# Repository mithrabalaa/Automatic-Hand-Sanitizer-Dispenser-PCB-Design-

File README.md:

# Automatic-Hand-Sanitizer-Dispenser-PCB-Design-

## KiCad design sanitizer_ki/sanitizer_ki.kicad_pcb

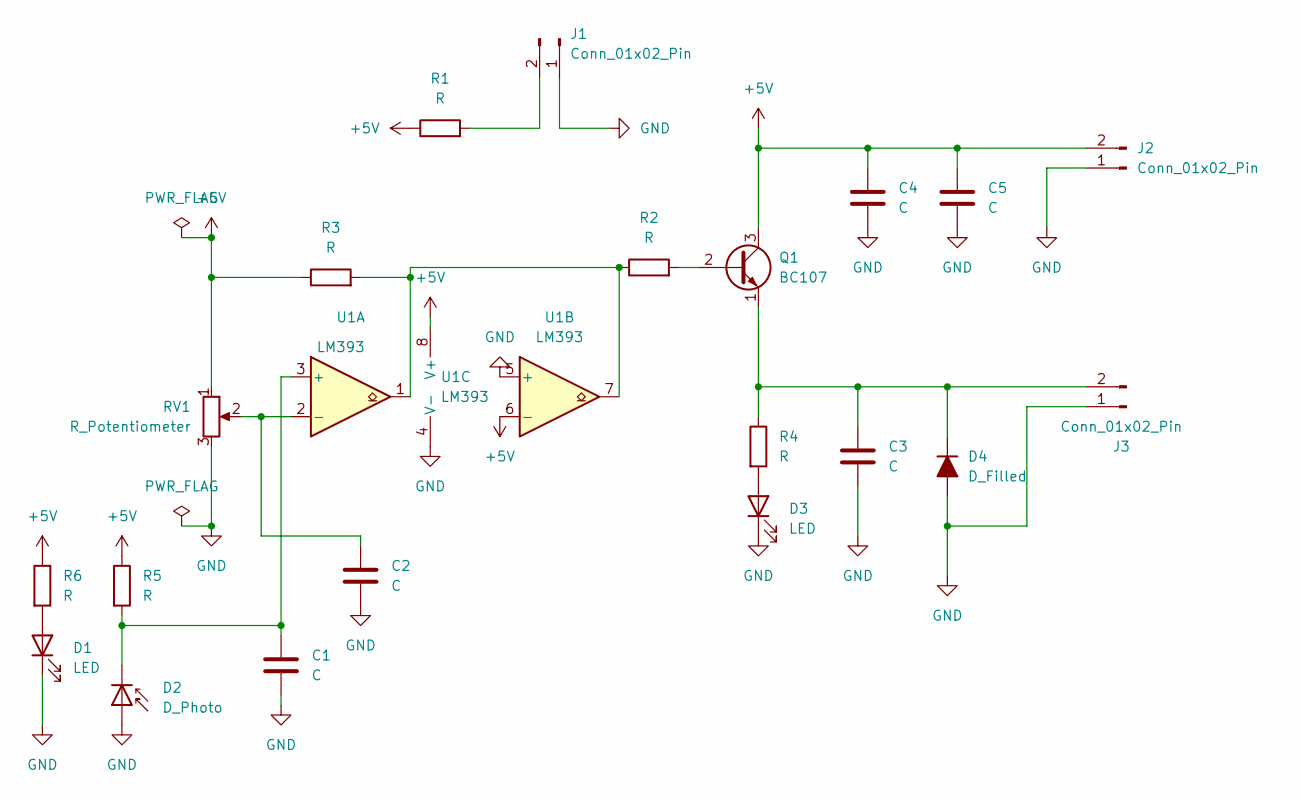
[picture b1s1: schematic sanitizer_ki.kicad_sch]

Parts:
C1, C2, C3, C4, C5: C; C_0201_0603Metric
D1, D3: LED; LED_D1.8mm_W1.8mm_H2.4mm_Horizontal_O1.27mm_Z1.6mm
D2: D_Photo; D_5KPW_P7.62mm_Vertical_AnodeUp
D4: D_Filled; D_0201_0603Metric
J1, J2, J3: Conn_01x02_Pin; PinHeader_1x02_P2.54mm_Vertical_SMD_Pin1Right
Q1: BC107; TO-18-3
R1, R2, R3, R4, R5, R6: R; R_0805_2012Metric_Pad1.20x1.40mm_HandSolder
RV1: R_Potentiometer; Potentiometer_ACP_CA9-V10_Vertical
U1: LM393; DIP-8-16_W7.62mm

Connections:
+5V: C4.1, C5.1, J2.2, Q1.3 (C), R1.1, R3.1, R5.1, R6.1, RV1.1, U1.6 (-), U1.8 (V+)
GND: C1.2, C2.2, C3.2, C4.2, C5.2, D1.1 (K), D2.2 (A), D3.1 (K), D4.2 (A), J1.1, J2.1, J3.1, RV1.3, U1.4 (V-), U1.5 (+)
unnamed: D1.2 (A), R6.2
unnamed: C1.1, D2.1 (K), R5.2, U1.3 (+)
unnamed: D3.2 (A), R4.2
unnamed: C3.1, D4.1 (K), J3.2, Q1.1 (E), R4.1
unnamed: J1.2, R1.2
unnamed: Q1.2 (B), R2.2
unnamed: R2.1, R3.2, U1.1, U1.7
unnamed: C2.1, RV1.2, U1.2 (-)

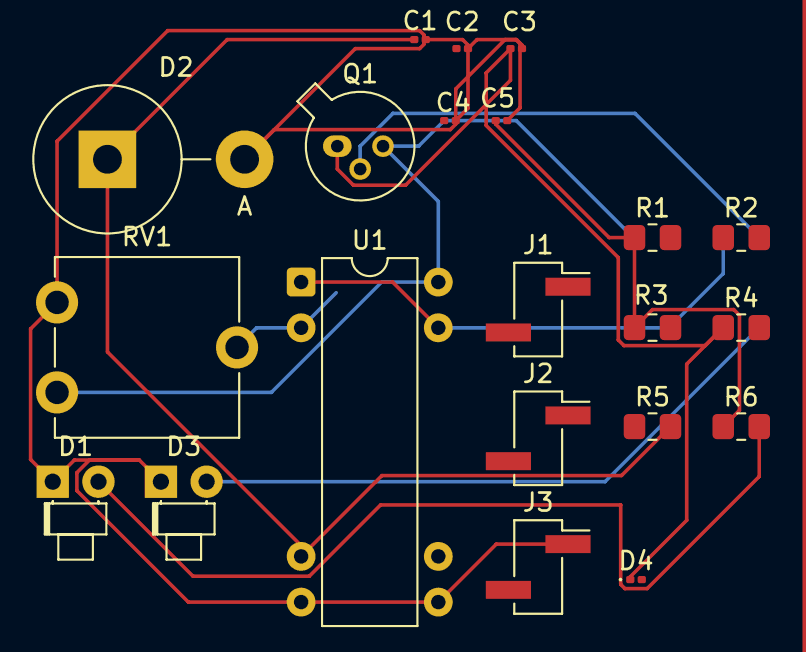
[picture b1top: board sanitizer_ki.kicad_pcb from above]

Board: 2 copper layers, 21 parts (0 on the bottom side), 10 nets.
